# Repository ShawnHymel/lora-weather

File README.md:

LoRa Weather Station
====================

LoRa client and server. Arduino reads temperature, humidity, and pressure data from BME280 sensor and sends it over a simple LoRa wireless connection to a Raspberry Pi.

Required Parts
--------------

 - [Arduino UNO](https://www.digikey.com/product-detail/en/A000066/1050-1024-ND/2784006/)
 - 2x [Adafruit RFM95W LoRa Breakout](https://www.digikey.com/product-detail/en/adafruit-industries-llc/3072/1528-1667-ND/6005357)
 - [Adafruit BME280 Breakout](https://www.digikey.com/product-detail/en/adafruit-industries-llc/2652/1528-1359-ND/5604372)
 - [Raspberry Pi 3 Model B+](https://www.digikey.com/product-detail/en/raspberry-pi/RASPBERRY-PI-3-MODEL-B/1690-1025-ND/8571724)
 - 2x [Breadboards](https://www.digikey.com/product-detail/en/bud-industries/BB-32621/377-2094-ND/4156445)
 - [Jumper wires](https://www.digikey.com/product-detail/en/global-specialties/WK-2/BKWK-2-ND/5231341)

Hardware Setup
--------------

Connect the Arduino as shown:

Connect the Raspberry Pi as shown:

Server Software
---------------

Install Raspbian (with Desktop) on the Raspberry Pi. From a console, run the following command to install the RFM9x Python package:

```
pip install adafruit-circuitpython-rfm9x
```

Go into the *Python* directory of this repo and run *lora-weather-server.py*.

```
python lora-weather-server.py
```

Arduino Software
----------------

Install the following libraries for Arduino:
 - [RadioHead v1.59](http://www.airspayce.com/mikem/arduino/RadioHead/)
 - [Adafruit_Sensor](https://github.com/adafruit/Adafruit_Sensor)
 - [Adafruit_BME280_Library](https://github.com/adafruit/Adafruit_BME280_Library)
 
Upload the *lora-weather-client.ino* to the Arduino (found in the *Arduino* directory of this repository).

Running
-------

The Arduino should begin sending temperature, humidity, and pressure data to the Raspberry Pi at regular intervals. Check the console output to see the sensor data.

License
-------

The code is beerware; if you see me at the local, and you've found the code helpful, please buy me a round!

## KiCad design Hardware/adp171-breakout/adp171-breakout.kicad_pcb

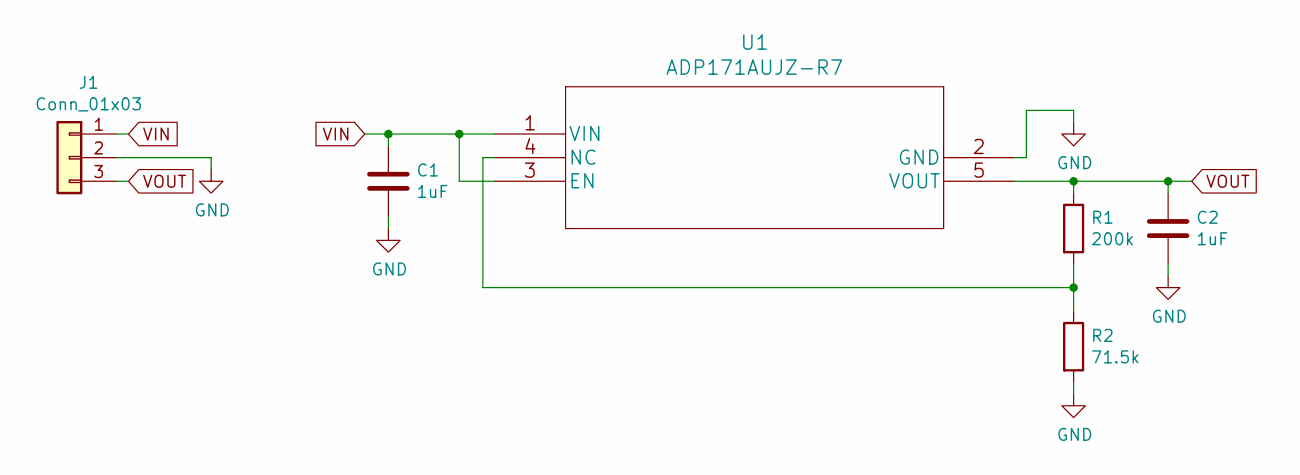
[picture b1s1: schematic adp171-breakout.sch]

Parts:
C1, C2: 1uF; C_0603_1608Metric
J1: Conn_01x03; PinHeader_1x03_P2.54mm_Vertical
R1: 200k; R_0603_1608Metric
R2: 71.5k; R_0603_1608Metric
U1: ADP171AUJZ-R7

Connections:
GND: C1.2, C2.2, J1.2, R2.2, U1.2 (GND)
unnamed: R1.2, R2.1, U1.4 (NC)
VIN: C1.1, J1.1, U1.1 (VIN), U1.3 (EN)
VOUT: C2.1, J1.3, R1.1, U1.5 (VOUT)

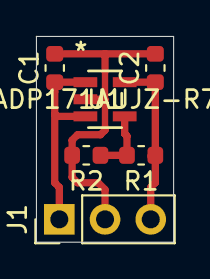
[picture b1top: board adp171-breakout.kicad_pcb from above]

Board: 2 copper layers, 7.6 x 11.4 mm, 6 parts (0 on the bottom side), 4 nets.

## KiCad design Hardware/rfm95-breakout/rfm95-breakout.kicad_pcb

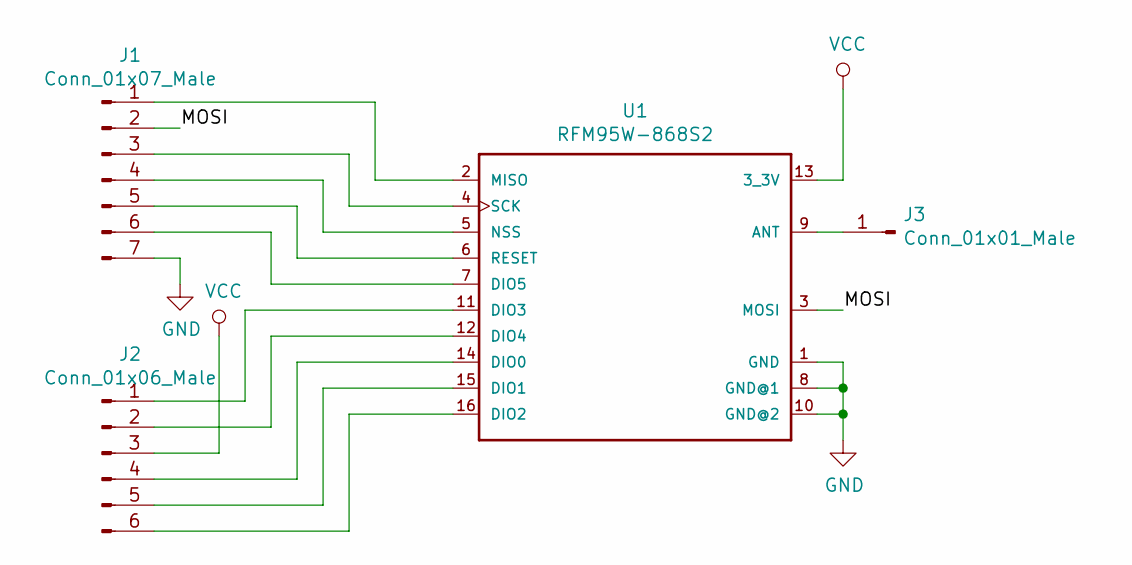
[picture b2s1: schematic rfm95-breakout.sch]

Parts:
J1: Conn_01x07_Male; PinHeader_1x07_P2.54mm_Vertical
J2: Conn_01x06_Male; PinHeader_1x06_P2.54mm_Vertical
J3: Conn_01x01_Male; PinHeader_1x01_P2.54mm_Vertical
U1: RFM95W-868S2; XCVR_RFM95W-868S2

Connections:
/MOSI: J1.2, U1.3 (MOSI)
GND: J1.7, U1.1 (GND), U1.8 (GND@1), U1.10 (GND@2)
unnamed: J1.1, U1.2 (MISO)
unnamed: J1.3, U1.4 (SCK)
unnamed: J1.4, U1.5 (NSS)
unnamed: J1.5, U1.6 (RESET)
unnamed: J1.6, U1.7 (DIO5)
unnamed: J2.1, U1.11 (DIO3)
unnamed: J2.2, U1.12 (DIO4)
unnamed: J2.4, U1.14 (DIO0)
unnamed: J2.5, U1.15 (DIO1)
unnamed: J2.6, U1.16 (DIO2)
unnamed: J3.1, U1.9 (ANT)
VCC: J2.3, U1.13 (3_3V)

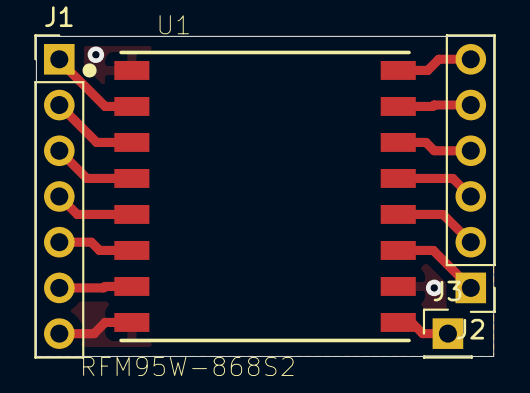
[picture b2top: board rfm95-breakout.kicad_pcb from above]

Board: 2 copper layers, 25.4 x 17.8 mm, 4 parts (0 on the bottom side), 14 nets.

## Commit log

2019-03-24 Added Python weather station
2019-03-29 Updated filenames for Python code
2019-03-29 Added Arduino files and README
2019-03-29 Added required packages lines in Python code
2019-04-08 Added images
2019-04-08 Added scaled images
2019-04-08 Updated readme and images
2019-04-08 Updated readme and images (again)
2019-05-09 Added rssi client test
2019-05-09 Added rssi test server code
2019-05-09 Moved rssi test server code
2019-05-22 Added ADP171 breakout
2019-06-05 Updated README with links
2019-07-25 Added INA212 breakout and code for ep 9

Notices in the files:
parts and their libraries:
Copyright 2016 Accelerated Designs. All rights reserved.
